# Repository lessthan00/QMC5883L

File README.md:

# QMC5883L  

封装 LGA16(3x3,p0.5) 可以焊接, 焊盘需要加长  
  
[datasheet](https://www.jlc-smt.com/lcsc/detail?componentCode=C976032)  
  
VDD 2.16V-3.6V  
VDDIO 1.65V-3.6V  
电流消耗 最大850uA  
16bit ADC  
the default  I2C address is 0D: 0001101    
DRDY : 数据准备好上拉,被读取下拉  
  
[模块参考](https://item.taobao.com/item.htm?abbucket=4&detail_redpacket_pop=true&id=670631408699&ltk2=1747749644070qp6qp09jpq23lzgjg8umnh&ns=1&priceTId=213e044f17477496188852615e1bc5&query=qmc5883l%E6%A8%A1%E5%9D%97&spm=a21n57.1.hoverItem.2&utparam=%7B%22aplus_abtest%22%3A%2288fea62abbedbf266e4b60de05d06fd2%22%7D&xxc=taobaoSearch)

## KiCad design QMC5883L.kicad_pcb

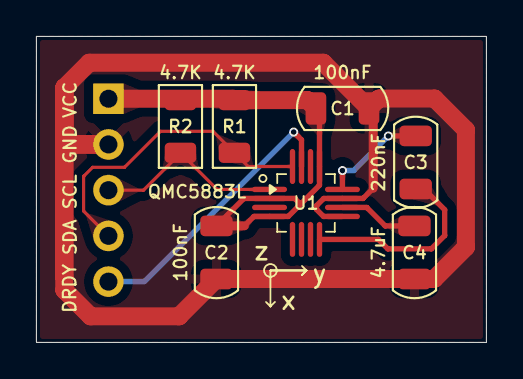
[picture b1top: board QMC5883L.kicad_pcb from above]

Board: 2 copper layers, 25.0 x 17.0 mm, 8 parts (1 on the bottom side), 8 nets.

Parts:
C1, C2: 100nF; C_1206_3216Metric
C3: 220nF; C_1206_3216Metric
C4: 4.7uF; C_1206_3216Metric
J1: Conn_01x05; PinHeader_1x05_P2.54mm_Vertical
R1, R2: 4.7K; R_1206_3216Metric
U1: QMC5883L; LGA-16_3x3mm_P0.5mm

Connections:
/DRDY: J1.5, U1.15 (DRDY)
/SCL: J1.3, R2.2, U1.1 (SCL)
/SDA: J1.4, R1.2, U1.16 (SDA)
GND: C1.2, C2.2, C4.2, J1.2, U1.9 (GND), U1.11 (GND)
unnamed: C4.1, U1.10 (C1)
unnamed: C3.2, U1.12 (SETC)
unnamed: C3.1, U1.8 (STEP)
VCC: C1.1, C2.1, J1.1, R1.1, R2.1, U1.2 (VDD), U1.4 (S1), U1.13 (VDDIO)
